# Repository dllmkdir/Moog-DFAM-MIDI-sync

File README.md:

# Moog-DFAM-MIDI-sync
Moog DFAM MIDI synchronization using Arduino.
You can configure your own **MOOG DFAM** to synchronize with your computer, using just an Arduino.

## Advice and Findings
Read carefully the Voltage Input Specs before implementing this solution.

We HIGHLY ENCOURAGE using an **Arduino Due** or Native USB Port options (Due, Leonardo, Zero, Micro) to recieve MIDI information.

Most of the non-USB-native microcontrollers need to use the Serial Port with [Hairless](https://projectgus.github.io/hairless-midiserial/).

Hairless is a program to communicate MIDI information, but it is not a robust solution to implement.

Hairless crashes, has multiple errors and can even freeze computers. In action, Hairless is more like a testing toy than a good way to mantain MIDI communication. Also, it creates huge lag gaps.

Current is not a big problem for the DFAM, because the input and output work with buffers to decouple impedance.

## Instructions
Using the libraries provided by the Arduino Team: 

[https://github.com/arduino-libraries/MIDIUSB](https://github.com/arduino-libraries/MIDIUSB)

First, download the MIDIUSB library available on Arduino. (version 1.0.3 is recommended)

We added the main src folder of this library just for reference. These are the most important files on the library.

Open The Arduino App and copy the code from the **"moog_sync.ino"** file.

Compile the Program, Upload it and you are good to go.

The Eagle Board is also included.

You can observe how the circuit needs to be configured in order to operate.

Connect the Arduino to the Native USB Port and configure the MIDI output in your Favorite DAW.

The device must appear as `Arduino Due`. 

After this, the MIDI trigger signal must be there. Check out if the Built-in LED reacts to the incoming MIDI Impulse.

I HIGHLY ENCOURAGE also to measure output voltage before connecting to the **Moog DFAM**. At least, it is incredibly expensive to just crash the whole device.

You must be getting voltages across 0.1 and 5 V.

Finally, Create a MIDI Track and send any note to trigger the MOOG DFAM.

Observe that the incoming note must be in a short duration to avoid multiple false triggers.

BAM! Now your Moog DFAM can sync to any MIDI sequence.

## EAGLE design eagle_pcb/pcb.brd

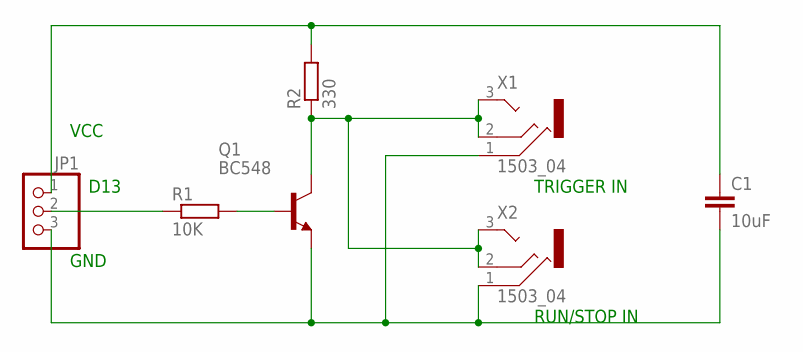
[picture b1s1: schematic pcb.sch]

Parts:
C1: 10uF; C050-035X075
JP1: PINHD-1X3; 1X03
Q1: BC548; TO92-EBC
R1: 10K; 0204/7
R2: 330; 0204/7
X1, X2: 1503_04

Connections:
unnamed: JP1.2, R1.1
unnamed: Q1.B, R1.2
unnamed: C1.1, JP1.1, R2.2
unnamed: C1.2, JP1.3, Q1.E, X1.1, X2.1
unnamed: Q1.C, R2.1, X1.2 (3), X1.3 (2), X2.2 (3), X2.3 (2)

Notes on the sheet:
RUN/STOP IN
TRIGGER IN
D13
GND
VCC

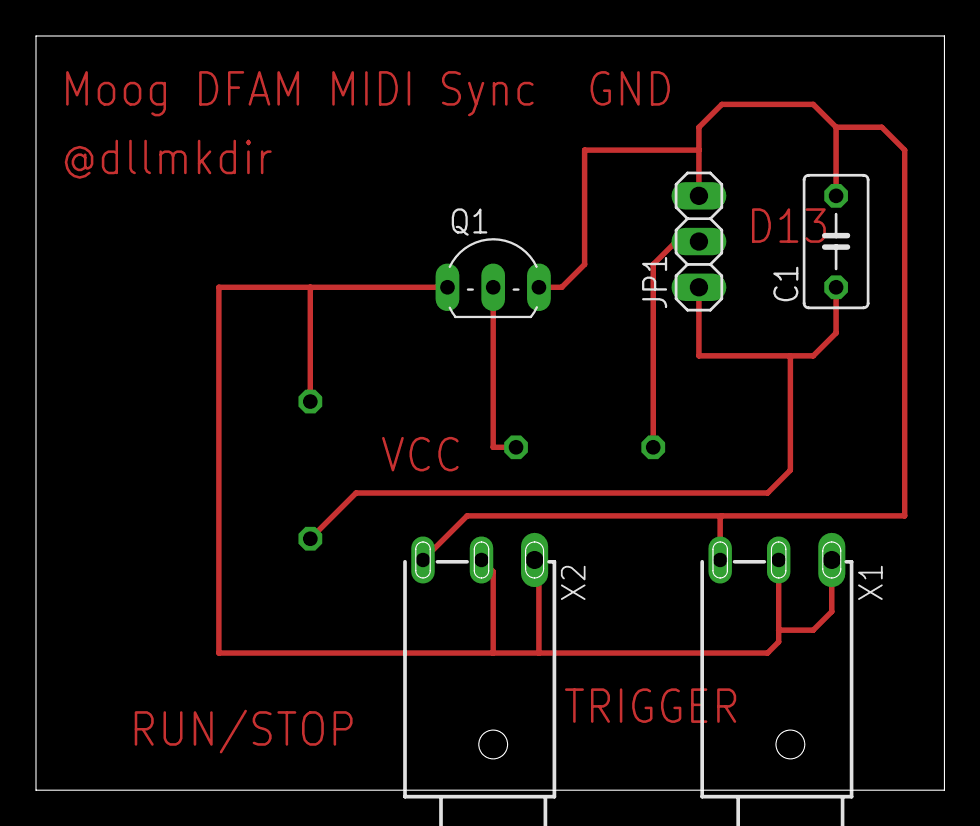
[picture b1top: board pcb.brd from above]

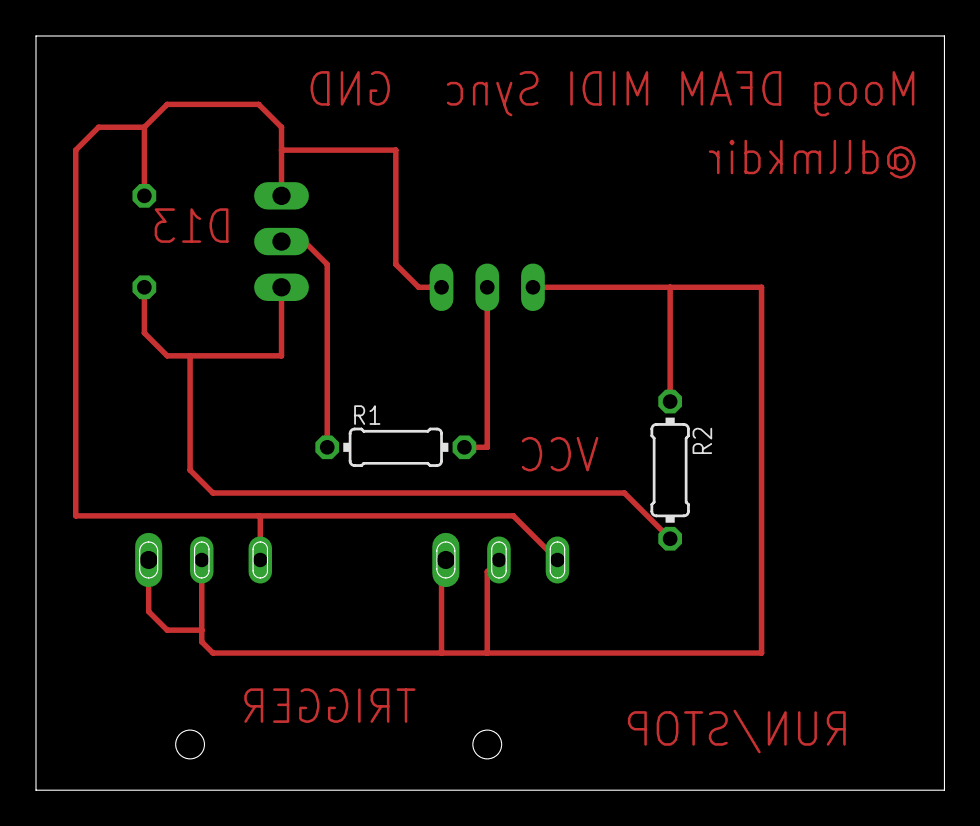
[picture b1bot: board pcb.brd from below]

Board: 2 copper layers, 50.5 x 41.9 mm, 7 parts (2 on the bottom side), 5 nets.

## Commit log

2019-09-15 Project Source Code
2019-09-16 adding README.md
2019-09-16 Adding Diagram and Eagle Files
2019-09-16 update README img
